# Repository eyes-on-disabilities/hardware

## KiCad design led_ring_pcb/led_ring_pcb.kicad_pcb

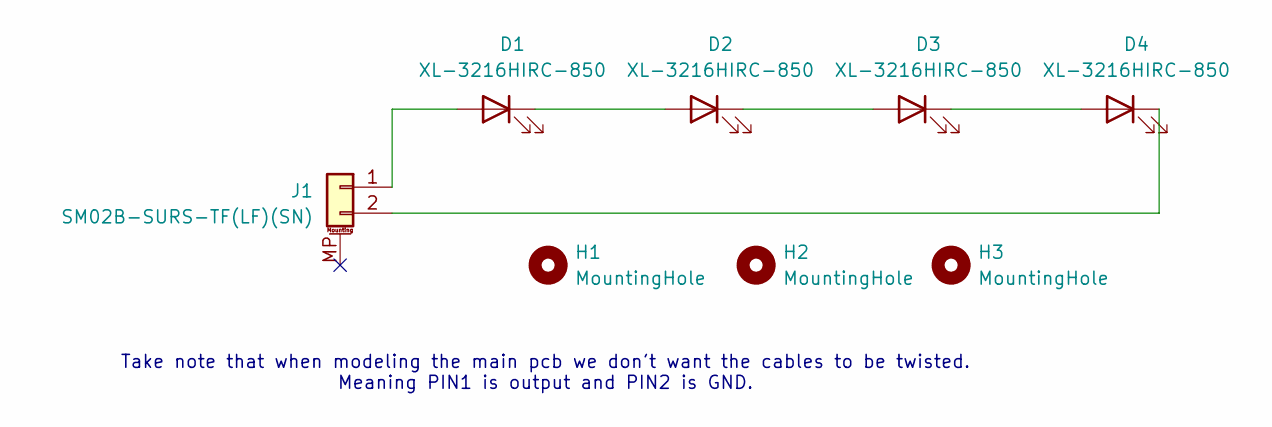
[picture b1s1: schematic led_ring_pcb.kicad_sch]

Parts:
D1, D2, D3, D4: XL-3216HIRC-850; LED_1206_3216Metric
H1, H2, H3: MountingHole; MountingHole_2mm
J1: SM02B-SURS-TF(LF)(SN); JST_SUR_SM02B-SURS-TF_1x02-1MP_P0.80mm_Horizontal

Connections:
unnamed: D1.2 (A), J1.1
unnamed: D1.1 (K), D2.2 (A)
unnamed: D2.1 (K), D3.2 (A)
unnamed: D3.1 (K), D4.2 (A)
unnamed: D4.1 (K), J1.2

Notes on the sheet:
Take note that when modeling the main pcb we don't want the cables to be twisted. Meaning PIN1 is output and PIN2 is GND.

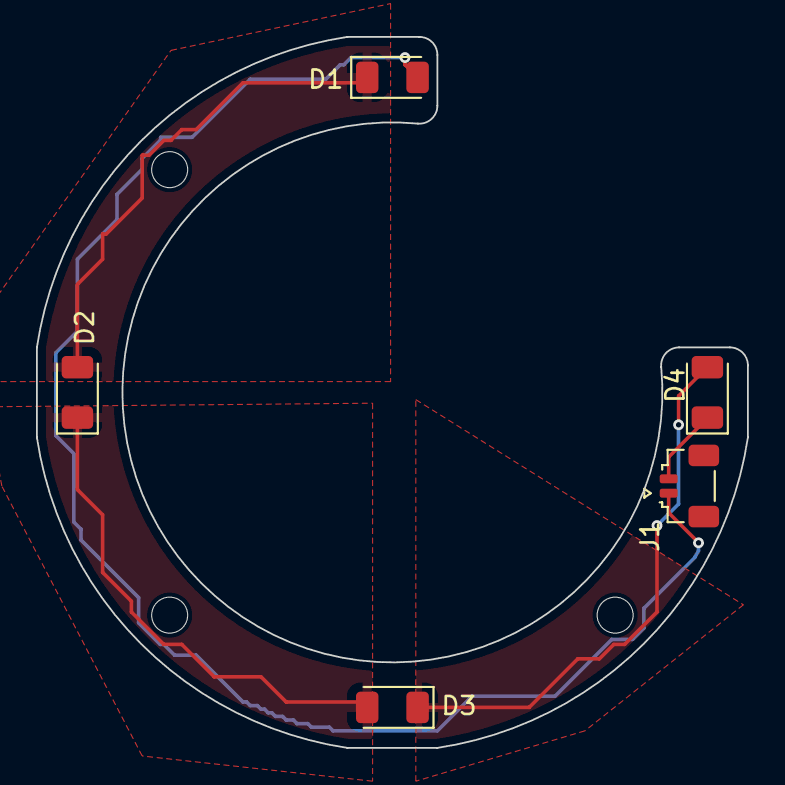
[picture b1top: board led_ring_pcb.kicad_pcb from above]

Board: 2 copper layers, 39.5 x 39.5 mm, 8 parts (0 on the bottom side), 5 nets.

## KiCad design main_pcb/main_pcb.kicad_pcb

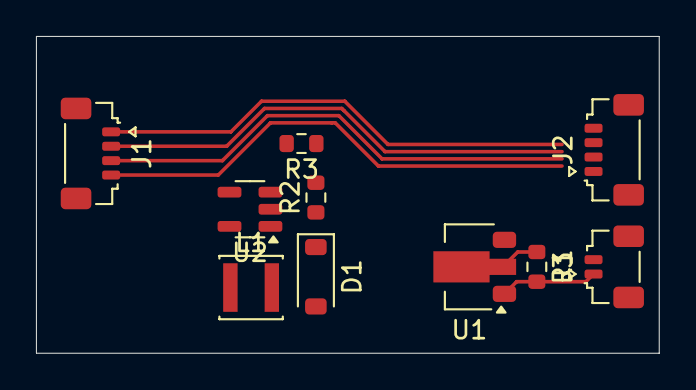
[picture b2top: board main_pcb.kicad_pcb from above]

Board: 2 copper layers, 34.6 x 17.6 mm, 10 parts (0 on the bottom side), 7 nets.

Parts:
D1: D; D_SOD-123
J1, J2: Conn_01x04_MountingPin; JST_SUR_SM04B-SURS-TF_1x04-1MP_P0.80mm_Horizontal
J3: Conn_01x02_MountingPin; JST_SUR_SM02B-SURS-TF_1x02-1MP_P0.80mm_Horizontal
L1: L; L_Changjiang_FNR3015S
R1: 536R; R_0603_1608Metric
R2, R3: R; R_0603_1608Metric
U1: LM317L_SOT-89; SOT-89-3
U2: TPS61040DBV; SOT-23-5

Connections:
GND: J3.2, R3.2, U2.2 (GND)
unnamed: D1.2 (A), L1.2, U2.1 (SW)
unnamed: D1.1 (K), R2.1
unnamed: J3.1, R1.2, U1.1 (ADJ)
unnamed: R1.1, U1.2 (VO)
unnamed: L1.1, U2.4 (EN), U2.5 (VIN)
unnamed: R2.2, R3.1, U2.3 (FB)

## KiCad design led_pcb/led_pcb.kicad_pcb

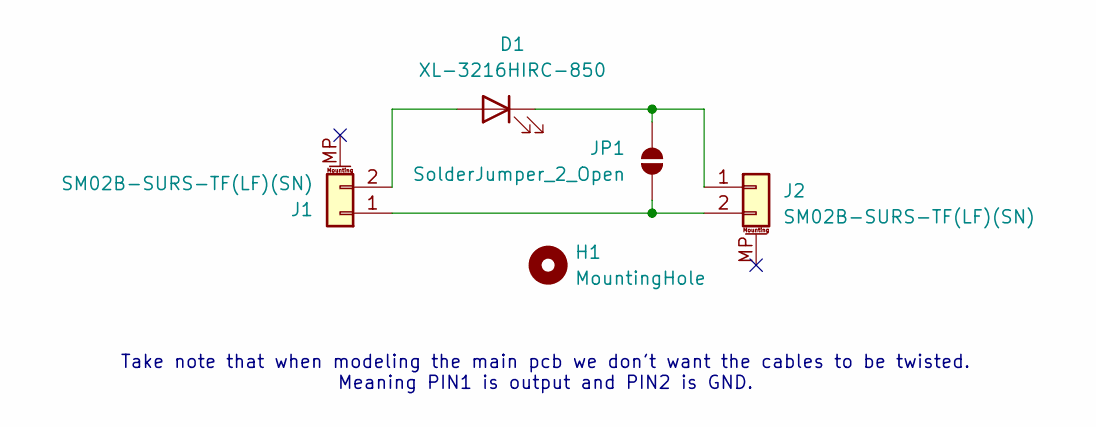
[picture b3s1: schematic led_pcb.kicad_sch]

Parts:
D1: XL-3216HIRC-850; LED_1206_3216Metric
H1: MountingHole; MountingHole_2mm
J1, J2: SM02B-SURS-TF(LF)(SN); JST_SUR_SM02B-SURS-TF_1x02-1MP_P0.80mm_Horizontal
JP1: SolderJumper_2_Open; SolderJumper-2_P1.3mm_Open_TrianglePad1.0x1.5mm

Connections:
unnamed: D1.2 (A), J1.2
unnamed: D1.1 (K), J2.1, JP1.2 (B)
unnamed: J1.1, J2.2, JP1.1 (A)

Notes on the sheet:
Take note that when modeling the main pcb we don't want the cables to be twisted. Meaning PIN1 is output and PIN2 is GND.

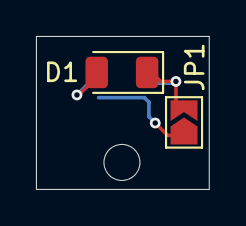
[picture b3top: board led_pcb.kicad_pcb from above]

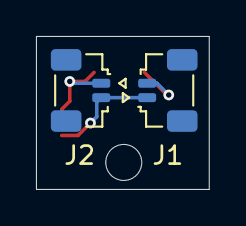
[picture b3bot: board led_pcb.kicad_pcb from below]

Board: 2 copper layers, 9.6 x 8.5 mm, 5 parts (2 on the bottom side), 3 nets.

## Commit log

2025-02-17 added led_pcb, led_ring_pcb and main_pcb. All WIP.
2025-08-28 added test to check push mirror
2025-08-28 removed test file again
